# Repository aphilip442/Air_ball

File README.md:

# Air_ball

Describes how to make a 3D printed air ball holder with mouse sensors to capture the ball's motion. 

Can be used in behavioral rigs with mice.

## Parts

* 3D printed parts: bottom and top
* M6 thread heat-insert: https://befr.rs-online.com/web/p/threaded-inserts/0278629/
* M4 thread heat-insert: https://befr.rs-online.com/web/p/threaded-inserts/0278607/
* M6 pneumatic push-in fitting: https://befr.rs-online.com/web/p/pneumatic-straight-fittings/1216041/
* Pressure regulator : SMC pneumatics - Model: ARM11A B3-208-J1: 
https://www.smc.eu/portal_ssl/WebContent/digital_catalog_2/jsp/view_product_configurator.jsp?dc_product_id=87018&part_number=ARM11AB3-508-J1
* 6mm tubing: https://www.smc.eu/portal_ssl/WebContent/digital_catalog_2/jsp/view_product_configurator.jsp?dc_product_id=54694&lang=fr&ctry=BE
* Warning: this assumes you have a source for pressured air

## How to assemble

* 3D print the components (black PLA)
* Heat-insert M4-M6 threads in the 3D parts with a soldering iron
* Put an M6 push-in fitting in the only hole that goes through the plastic
* Use epoxy to glue bottom and top parts

# Motion Sensors 
## Parts

* 2x 3D printed parts: sensor holder 
* 2x Motion sensor PMW3360: https://www.tindie.com/products/jkicklighter/pmw3360-motion-sensor/
* 2x Arduino Micro
* 1x Arduino Due
* 1x PCB

## Power

Both board types take 12V on Vin and share the same GND.

## How to connect sensors to Micros

Pinout Sensor - Micro:
-------
* RS --- (NONE)
* GD --- GND
* MT --- Pin 7 (PE6, INT6) -> movement interrupt
* SS --- Pin 10 (PB6)
* SC --- SCK (PB1)
* MO --- MOSI (PB2)
* MI --- MISO (PB3)
* VI --- 5V

https://www.tindie.com/products/jkicklighter/pmw3360-motion-sensor/

## How to connect Micros to Due

We are using the serial ports and the Due provides power.

WARNING: the Due works on 3.3V and the Micros on 5V.

Pinout Due - Micro
-------
* RX  = voltage divider from TX (5V(micro)->3.3V(due), use 2k and 1k resistors)

# Micro's output

XY motion from the sensor, sampled at around 1kHz

# Due's output

Yaw - pitch - roll values (you can add eventual other outputs like the total distance)

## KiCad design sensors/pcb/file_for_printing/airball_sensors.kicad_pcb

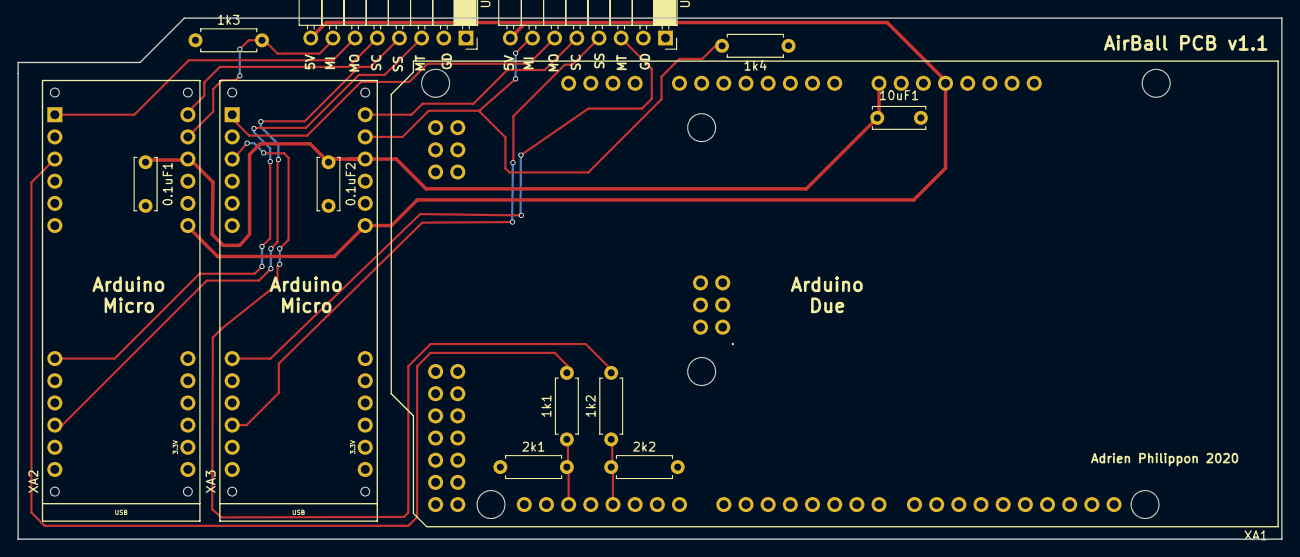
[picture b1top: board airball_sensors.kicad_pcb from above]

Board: 2 copper layers, 144.8 x 59.7 mm, 14 parts (0 on the bottom side), 17 nets.

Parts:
0.1uF1, 0.1uF2, 10uF1: C; C_Disc_D6.0mm_W2.5mm_P5.00mm
1k1, 1k2, 1k3, 1k4, 2k1, 2k2: R; R_Axial_DIN0207_L6.3mm_D2.5mm_P7.62mm_Horizontal
U1, U2: PWM3360_Motion_Sensor; Socket_Strip_Angled_1x08_Pitch2.54mm
XA1: Arduino_Due_Shield
XA2, XA3: Arduino_Micro_Socket

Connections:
+5V: U1.8, U2.8, XA1.5V1, XA2.5V, XA3.5V
+12V: 0.1uF1.1, 0.1uF2.1, 10uF1.1, XA1.VIN, XA2.VIN, XA3.VIN
/MI_1: 1k3.2, U1.7, XA2.MISO
/MI_2: 1k4.2, U2.7, XA3.MISO
/MO_1: U1.6, XA2.MOSI
/MO_2: U2.6, XA3.MOSI
/MT_1: U1.3, XA2.D7
/MT_2: U2.3, XA3.D7
/SC_1: U1.5, XA2.SCK
/SC_2: U2.5, XA3.SCK
/SS_1: U1.4, XA2.D10
/SS_2: U2.4, XA3.D10
/TX_MICRO_1: 1k1.2, XA2.D1
/TX_MICRO_2: 1k2.2, XA3.D1
GND: 0.1uF1.2, 0.1uF2.2, 1k3.1, 1k4.1, 2k1.1, 2k2.2, 10uF1.2, U1.2, U2.2, XA1.GND1, XA1.GND2, XA1.GND3, XA1.GND5, XA1.GND6, XA2.GND1, XA2.GND2, XA3.GND1, XA3.GND2
unnamed: 1k1.1, 2k1.2, XA1.D19
unnamed: 1k2.1, 2k2.1, XA1.D17

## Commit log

2019-11-22 Added gif
2019-11-22 Added video
2019-11-22 text
2019-11-24 Additional instructions
2019-11-24 Added PCB layout
2020-09-15 reorganized folder
2020-09-15 PCB v1.1
